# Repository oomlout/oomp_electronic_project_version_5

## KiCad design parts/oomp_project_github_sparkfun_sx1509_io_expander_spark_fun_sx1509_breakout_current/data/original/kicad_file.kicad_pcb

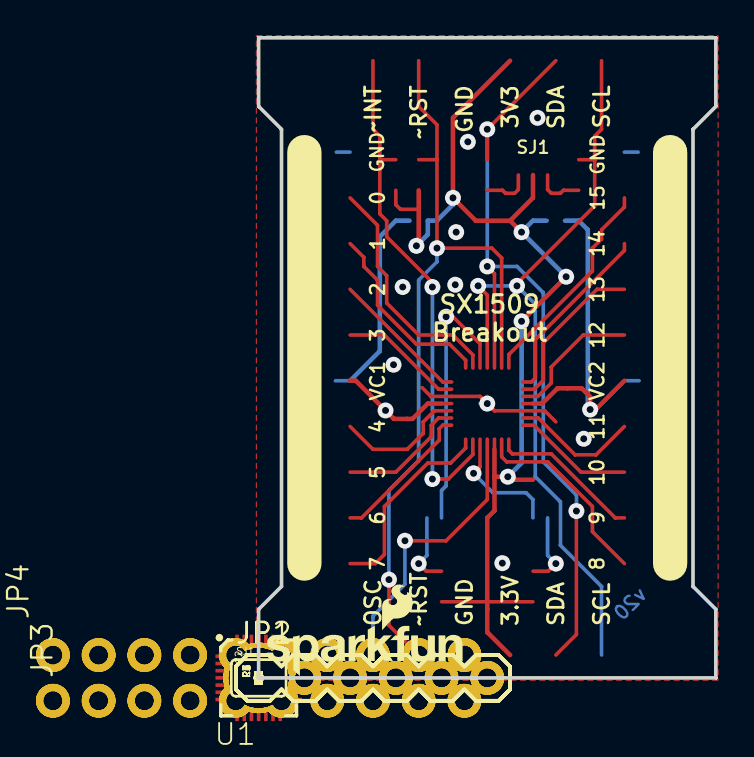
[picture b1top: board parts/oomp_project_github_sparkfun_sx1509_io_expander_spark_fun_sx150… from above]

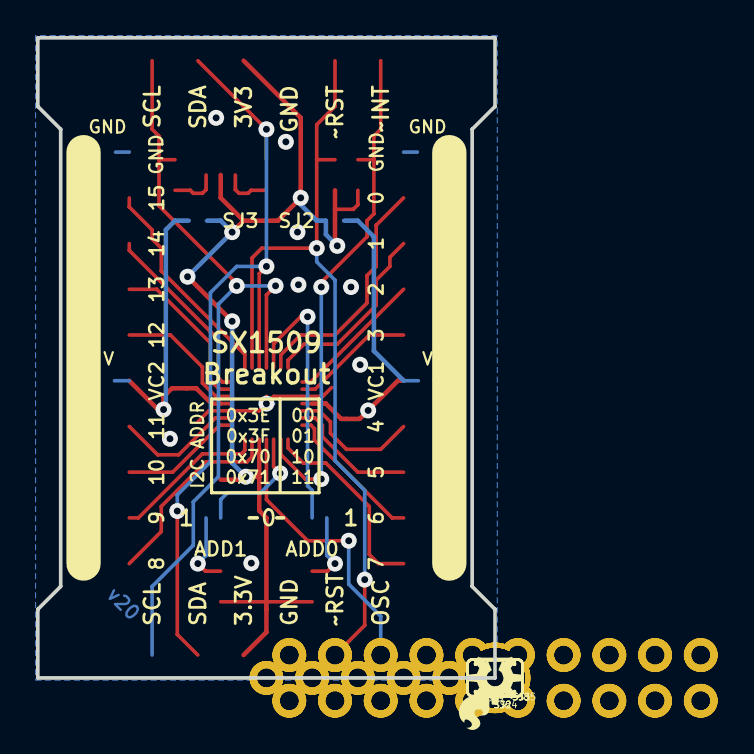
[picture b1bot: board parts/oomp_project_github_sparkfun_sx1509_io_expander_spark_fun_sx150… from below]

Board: 2 copper layers, 25.4 x 35.6 mm, 33 parts (10 on the bottom side), 33 nets.

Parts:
C1, C2, C3: 0.1uF; 0603-CAP
FRAME1: CREATIVE_COMMONS
JP1, JP2: 1X06
JP3, JP4: 2X10_ROUND_NOSILK
JP9, JP10: FIDUCIAL1X2; FIDUCIAL-1X2
LOGO1: SFE_LOGO_NAME_FLAME.1_INCH; SFE_LOGO_NAME_FLAME_.1
LOGO2: SFE_LOGO_FLAME.1_INCH; SFE_LOGO_FLAME_.1
LOGO3: OSHW-LOGOS; OSHW-LOGO-S
R1, R2, R3, R4, R5, R6: 10K; 0603-RES
SJ1: PAD-JUMPER-3-3OF3_NC_BY_TRACE_YES_SILK_FULL_BOX
SJ2: VCC1-3.3V; PAD-JUMPER-2-NC_BY_TRACE_YES_SILK
SJ3: VCC2-3.3V; PAD-JUMPER-2-NC_BY_TRACE_YES_SILK
SJ4, SJ5: PAD-JUMPER-3-2OF3_NC_BY_TRACE_YES_SILK_FULL_BOX
SJ6: A-VCC1; PAD-JUMPER-2-NO_NO_SILK
SJ7, SJ9: GND; PAD-JUMPER-2-NC_BY_TRACE_NO_SILK
SJ8: B-VCC2; PAD-JUMPER-2-NO_NO_SILK
STANDOFF1, STANDOFF2, STANDOFF3, STANDOFF4: STAND-OFF
U1: SX1509; QFN-28

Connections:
0: JP3.4, U1.27
1: JP3.6, U1.28
2: JP3.8, U1.1
3: JP3.10, U1.2
3.3V: C1.1, JP1.4, JP2.4, R1.2, R3.2, R5.2, R6.2, SJ1.2, SJ2.2, SJ3.2, U1.12
4: JP3.14, U1.5
5: JP3.16, U1.6
6: JP3.18, U1.7
7: JP3.20, U1.8
8: JP4.2, U1.13
9: JP4.4, U1.14
10: JP4.6, U1.15
11: JP4.8, U1.16
12: JP4.12, U1.19
13: JP4.14, U1.20
14: JP4.16, U1.21
15: JP4.18, U1.22
ADDR0: SJ4.2, U1.26
ADDR1: SJ5.2, U1.10
GND: C1.2, C2.2, C3.2, JP1.3, JP2.3, JP3.2, JP4.20, SJ4.3, SJ5.3, SJ7.1, SJ9.1, U1.3, U1.17, U1.29
unnamed: R2.2, SJ1.3
unnamed: R4.2, SJ1.1
unnamed: JP4.1, JP4.3, JP4.5, JP4.7, JP4.9, JP4.11, JP4.13, JP4.15, JP4.17, JP4.19, SJ8.1, SJ9.2
unnamed: R5.1, SJ4.1
unnamed: R6.1, SJ5.1
OSCIO: JP2.1, U1.11
PWRBUSA: JP3.1, JP3.3, JP3.5, JP3.7, JP3.9, JP3.11, JP3.13, JP3.15, JP3.17, JP3.19, SJ6.1, SJ7.2
SCL: JP1.6, JP2.6, R2.1, U1.25
SDA: JP1.5, JP2.5, R4.1, U1.24
VCC1: C2.1, JP3.12, SJ2.1, SJ6.2, U1.4
VCC2: C3.1, JP4.10, SJ3.1, SJ8.2, U1.18
~INT: JP1.1, R1.1, U1.9
~RESET: JP1.2, JP2.2, R3.1, U1.23

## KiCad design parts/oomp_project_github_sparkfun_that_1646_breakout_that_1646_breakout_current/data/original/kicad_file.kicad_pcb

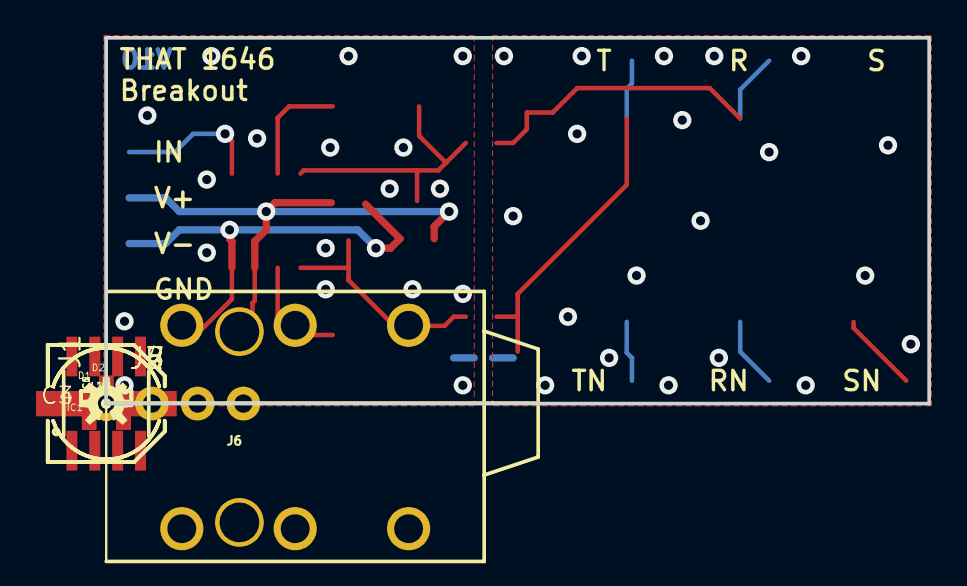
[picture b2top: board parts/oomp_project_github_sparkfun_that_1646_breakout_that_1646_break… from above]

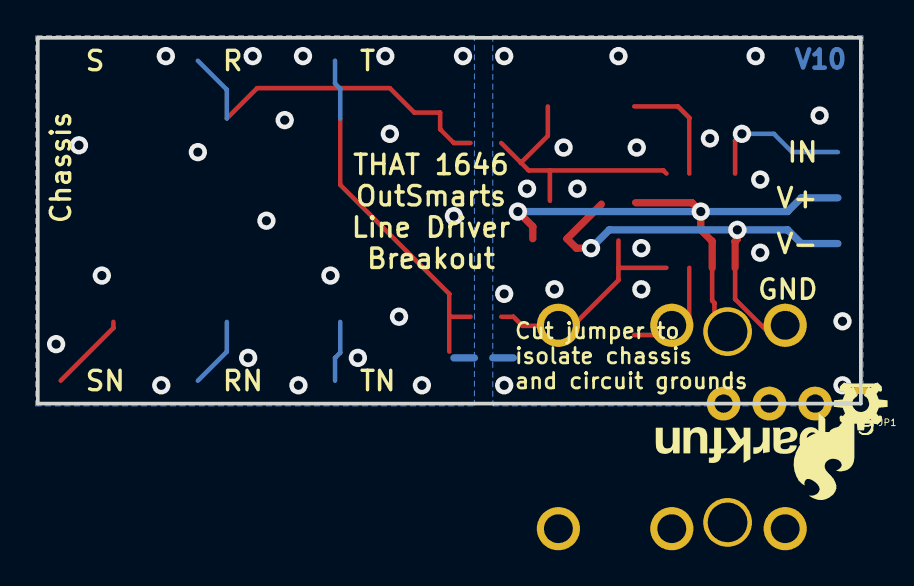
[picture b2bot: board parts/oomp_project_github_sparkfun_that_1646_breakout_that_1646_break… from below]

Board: 2 copper layers, 45.7 x 20.3 mm, 30 parts (8 on the bottom side), 14 nets.

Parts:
C1, C2: 0.1uF; 0603-CAP
C3, C4: 10uf NP; PANASONIC_D
C5, C6: 100pF; 0603-CAP
D1, D2: BAV99; SOT23-3
FD1, FD2, FD3, FD4: FIDUCIALUFIDUCIAL; MICRO-FIDUCIAL
FRAME1: FRAME-LETTER; CREATIVE_COMMONS
IC1: THAT1646; SO08
J1: 1x4; 1X04_NO_SILK_ALL_ROUND
J2: SN; 1X01_NO_SILK
J3: S; 1X01_NO_SILK
J4: TN; 1X01_NO_SILK
J5: RN; 1X01_NO_SILK
J6: OUTPUT; AUDIO_JACK_0.25__TRS_PTH_RA
J7: T; 1X01_NO_SILK
J8: R; 1X01_NO_SILK
J9: Chassis; 1X01_NO_SILK
JP1: GND-JOIN; PAD-JUMPER-2-NC_BY_TRACE_YES_SILK
L1, L2: 27uH; 0603
LOGO1, LOGO2: OSHW-LOGOS; OSHW-LOGO-S
LOGO4: SFE_LOGO_FLAME.2_INCH; SFE_LOGO_FLAME_.2
LOGO5: SFE_LOGO_NAME.1_INCH; SFE_LOGO_NAME_.1

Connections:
GND: C1.1, C2.1, IC1.3, J1.1, JP1.2
GND-ISO: C5.2, C6.2, J3.1, J6.SLEEVE, J9.1, JP1.1
unnamed: J5.1, J6.RING-NORM
unnamed: J4.1, J6.TIP-NORM
unnamed: J2.1, J6.SLEEVE-NORM
unnamed: C5.1, J6.TIP, J7.1, L2.2
unnamed: C6.1, J6.RING, J8.1, L1.2
unnamed: C3.-, D1.3, IC1.8, L2.1
unnamed: C4.-, D2.3, IC1.1, L1.1
unnamed: C4.+, IC1.2
unnamed: C3.+, IC1.7
unnamed: IC1.4, J1.4
VCC: C1.2, D1.2, D2.2, IC1.6, J1.3
VNEG: C2.2, D1.1, D2.1, IC1.5, J1.2

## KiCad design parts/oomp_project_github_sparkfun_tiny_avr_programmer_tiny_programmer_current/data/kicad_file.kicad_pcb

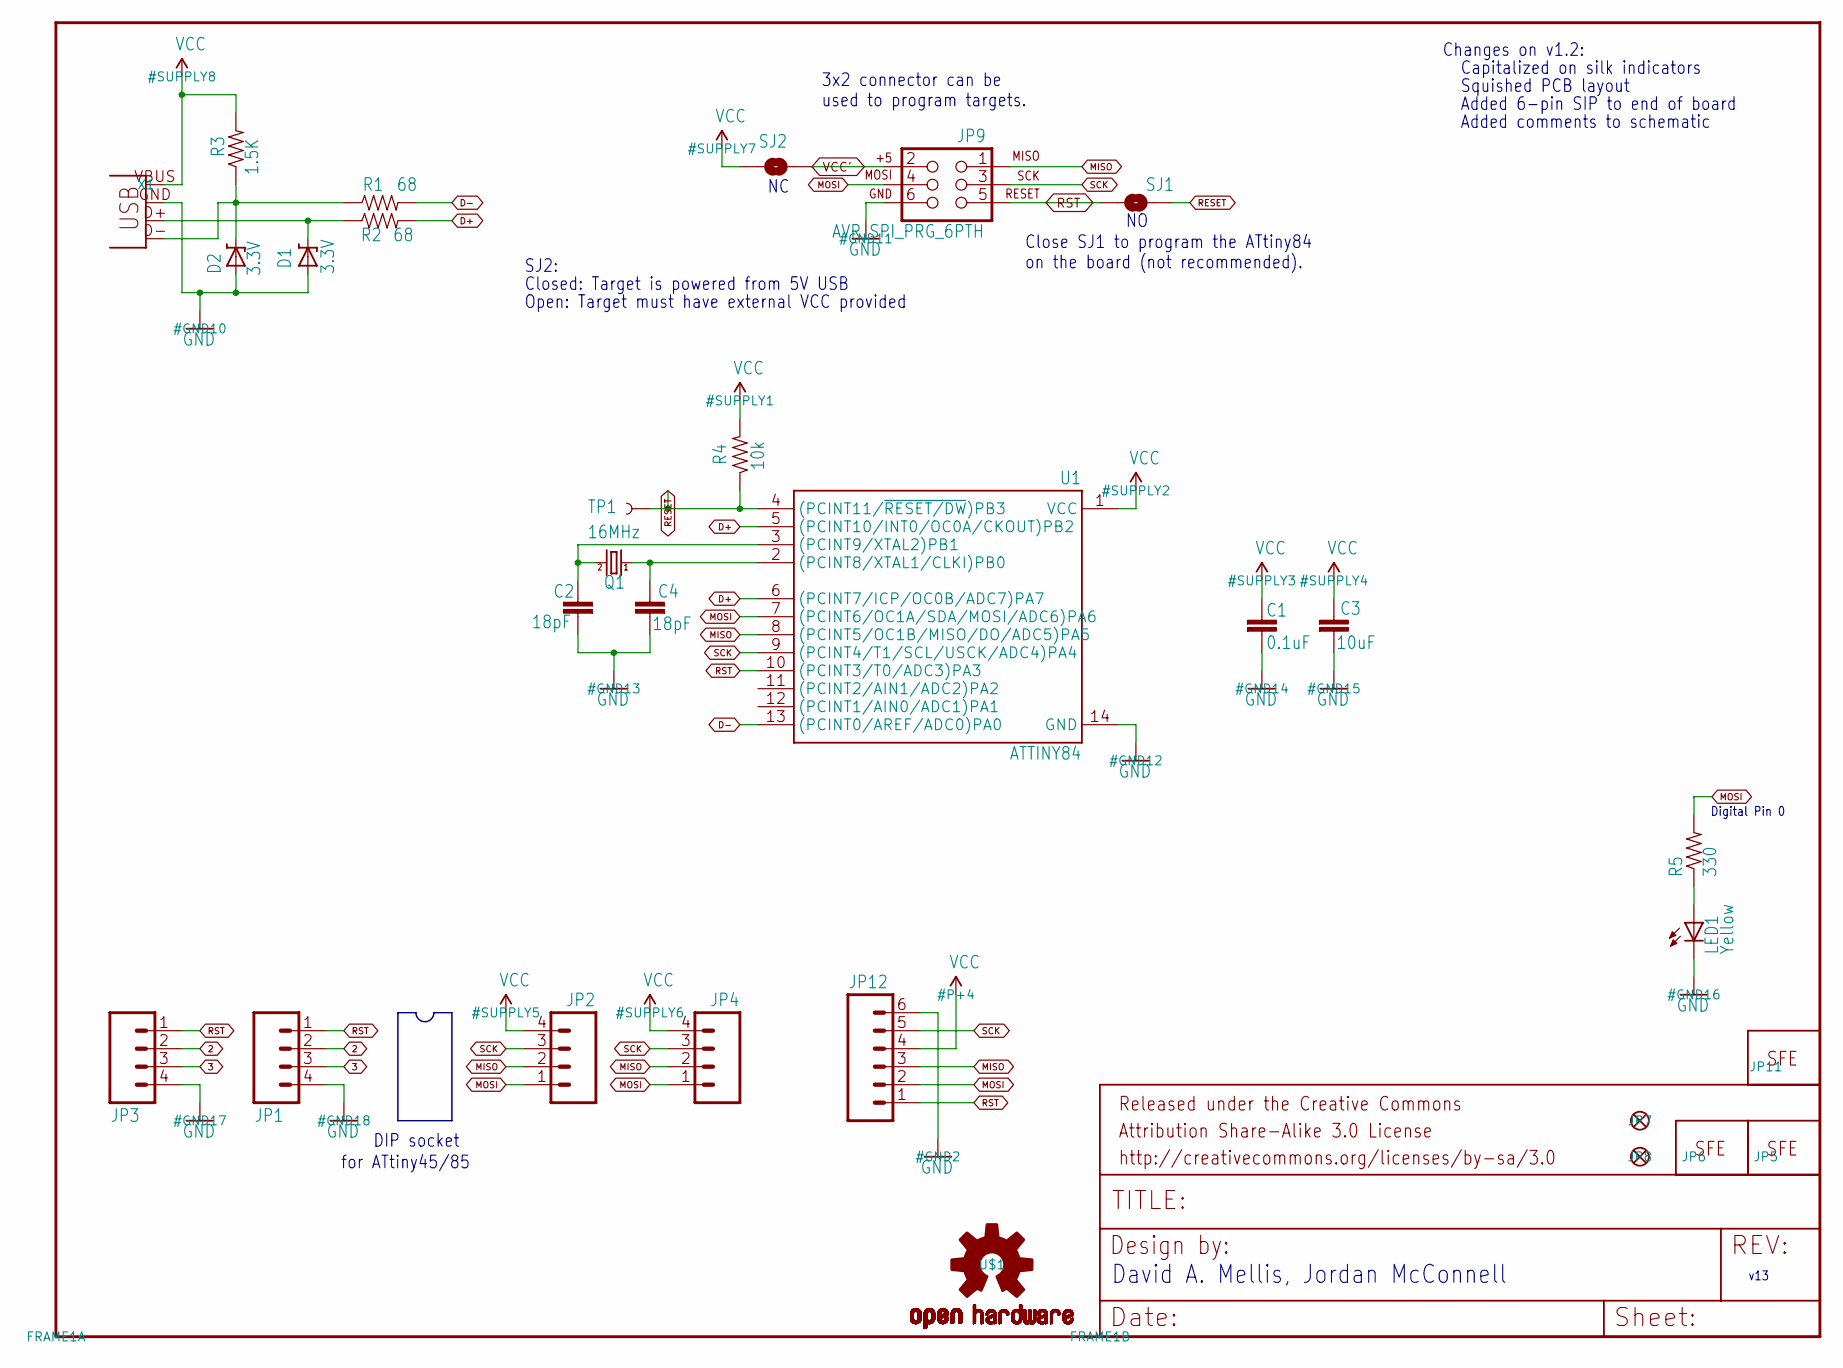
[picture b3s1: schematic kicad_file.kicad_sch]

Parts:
C1: 0.1uF; 0402-CAP
C2, C4: 18pF; 0402-CAP
C3: 10uF; 0402-CAP
D1, D2: 3.3V; SOD-323
FRAME1: FRAME-LETTER; CREATIVE_COMMONS
JP1, JP2: M04PTH; 1X04
JP3, JP4: M04SMD_STRAIGHT_COMBO; 1X04_SMD_STRAIGHT_COMBO
JP5: LOGO-SFENW2; SFE-NEW-WEB
JP6, JP11: LOGO-SFESK; SFE-LOGO-FLAME
JP7, JP8: FIDUCIALUFIDUCIAL; MICRO-FIDUCIAL
JP9: AVR_SPI_PRG_6PTH; 2X3
JP12: M06SIP; 1X06
LED1: Yellow; LED-0603
Q1: 16MHz; CRYSTAL-SMD-5X3
R1, R2: 68; 0402-RES
R3: 1.5K; 0402-RES
R4: 10k; 0402-RES
R5: 330; 0402-RES
SJ1: SOLDERJUMPERNO; SJ_2S-NO
SJ2: NC; SJ_2S
TP1: TEST-POINT3; PAD.03X.03
U1: ATTINY84; SO14
U$1: OSHW-LOGOS; OSHW-LOGO-S
X1: USB-A-H

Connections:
2: JP1.2, JP3.2
3: JP1.3, JP3.3
D+: R2.2, U1.5 ((PCINT10/INT0/OC0A/CKOUT)PB2), U1.6 ((PCINT7/ICP/OC0B/ADC7)PA7)
D-: R1.2, U1.13 ((PCINT0/AREF/ADC0)PA0)
GND: C1.2, C2.2, C3.2, C4.2, D1.2 (A), D2.2 (A), JP1.4, JP3.4, JP9.6, JP12.6, LED1.C, U1.14 (GND), X1.GND (VBUS)
MISO: JP2.2, JP4.2, JP9.1, JP12.3, U1.8 ((PCINT5/OC1B/MISO/DO/ADC5)PA5)
MOSI: JP2.1, JP4.1, JP9.4, JP12.2, R5.2, U1.7 ((PCINT6/OC1A/SDA/MOSI/ADC6)PA6)
unnamed: D2.1 (C), R1.1, R3.1, X1.D- (D+)
unnamed: D1.1 (C), R2.1, X1.D+ (D-)
unnamed: C2.1, Q1.3 (2), U1.3 ((PCINT9/XTAL2)PB1)
unnamed: C4.1, Q1.1, U1.2 ((PCINT8/XTAL1/CLKI)PB0)
unnamed: LED1.A, R5.1
RESET: R4.1, SJ1.1, TP1.P$1, U1.4 ((PCINT11/~RESET/DW)PB3)
RST: JP1.1, JP3.1, JP9.5, JP12.1, SJ1.2, U1.10 ((PCINT3/T0/ADC3)PA3)
SCK: JP2.3, JP4.3, JP9.3, JP12.5, U1.9 ((PCINT4/T1/SCL/USCK/ADC4)PA4)
VCC: C1.1, C3.1, JP2.4, JP4.4, JP12.4, R3.2, R4.2, SJ2.1, U1.1 (VCC), X1.VBUS (GND)
VCC': JP9.2, SJ2.2

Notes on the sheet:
Closed: Target is powered from 5V USB
v13
Added comments to schematic
Open: Target must have external VCC provided
Added 6-pin SIP to end of board
Close SJ1 to program the ATtiny84 on the board (not recommended).
Digital Pin 0
SJ2:
DIP socket
for ATtiny45/85
Squished PCB layout
Capitalized on silk indicators
David A. Mellis, Jordan McConnell
Changes on v1.2:
3x2 connector can be used to program targets.

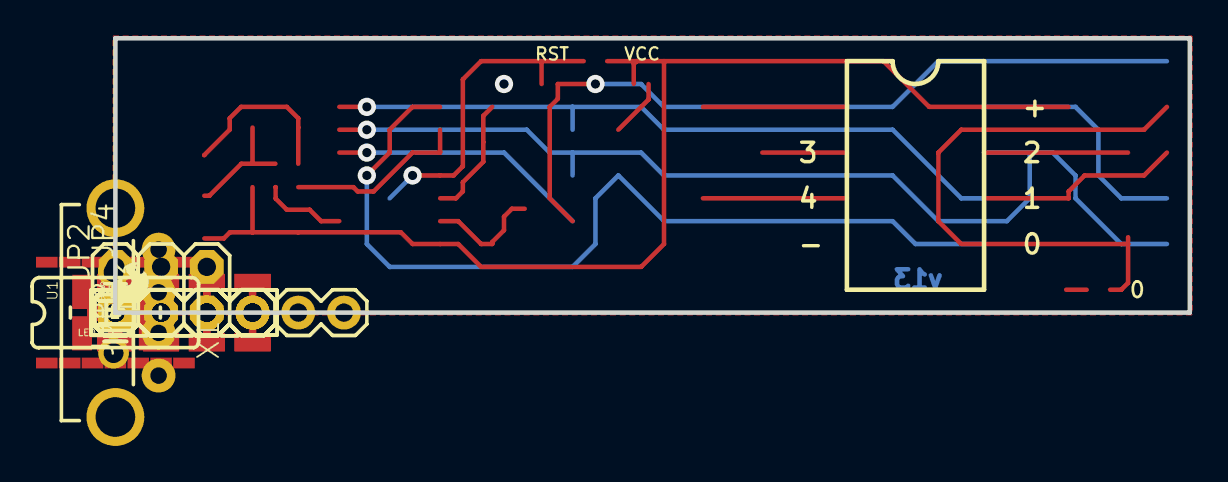
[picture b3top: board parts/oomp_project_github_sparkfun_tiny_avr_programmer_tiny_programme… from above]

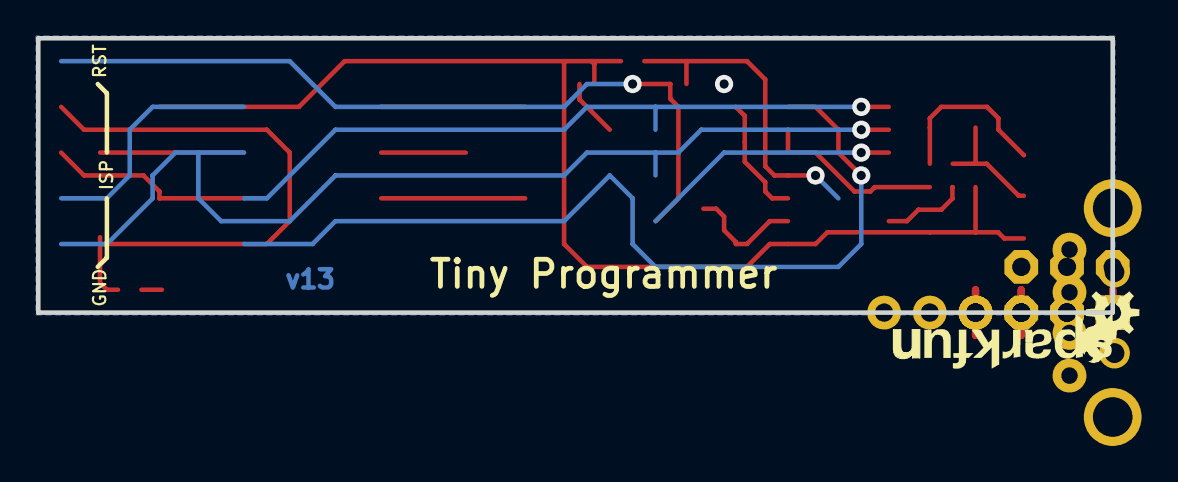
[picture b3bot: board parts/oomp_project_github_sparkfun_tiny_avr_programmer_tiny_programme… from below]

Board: 2 copper layers, 59.7 x 15.2 mm, 31 parts (4 on the bottom side), 17 nets.

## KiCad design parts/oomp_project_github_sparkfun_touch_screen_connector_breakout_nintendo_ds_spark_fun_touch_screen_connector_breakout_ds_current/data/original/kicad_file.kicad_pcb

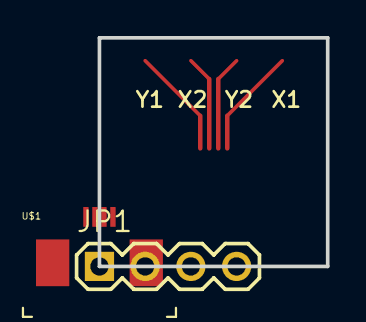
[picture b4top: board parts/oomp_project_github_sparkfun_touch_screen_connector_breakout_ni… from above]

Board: 16 copper layers, 12.7 x 12.7 mm, 5 parts (1 on the bottom side), 4 nets.

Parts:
FID1, FID2: FIDUCIAL1X2; FIDUCIAL-1X2
JP1: 1X04
U$1: DS_TOUCH_CONNECTOR
U$2: LOGO-SFESK; SFE-LOGO-FLAME

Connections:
unnamed: JP1.4, U$1.X1
unnamed: JP1.3, U$1.Y2
unnamed: JP1.2, U$1.X2
unnamed: JP1.1, U$1.Y1

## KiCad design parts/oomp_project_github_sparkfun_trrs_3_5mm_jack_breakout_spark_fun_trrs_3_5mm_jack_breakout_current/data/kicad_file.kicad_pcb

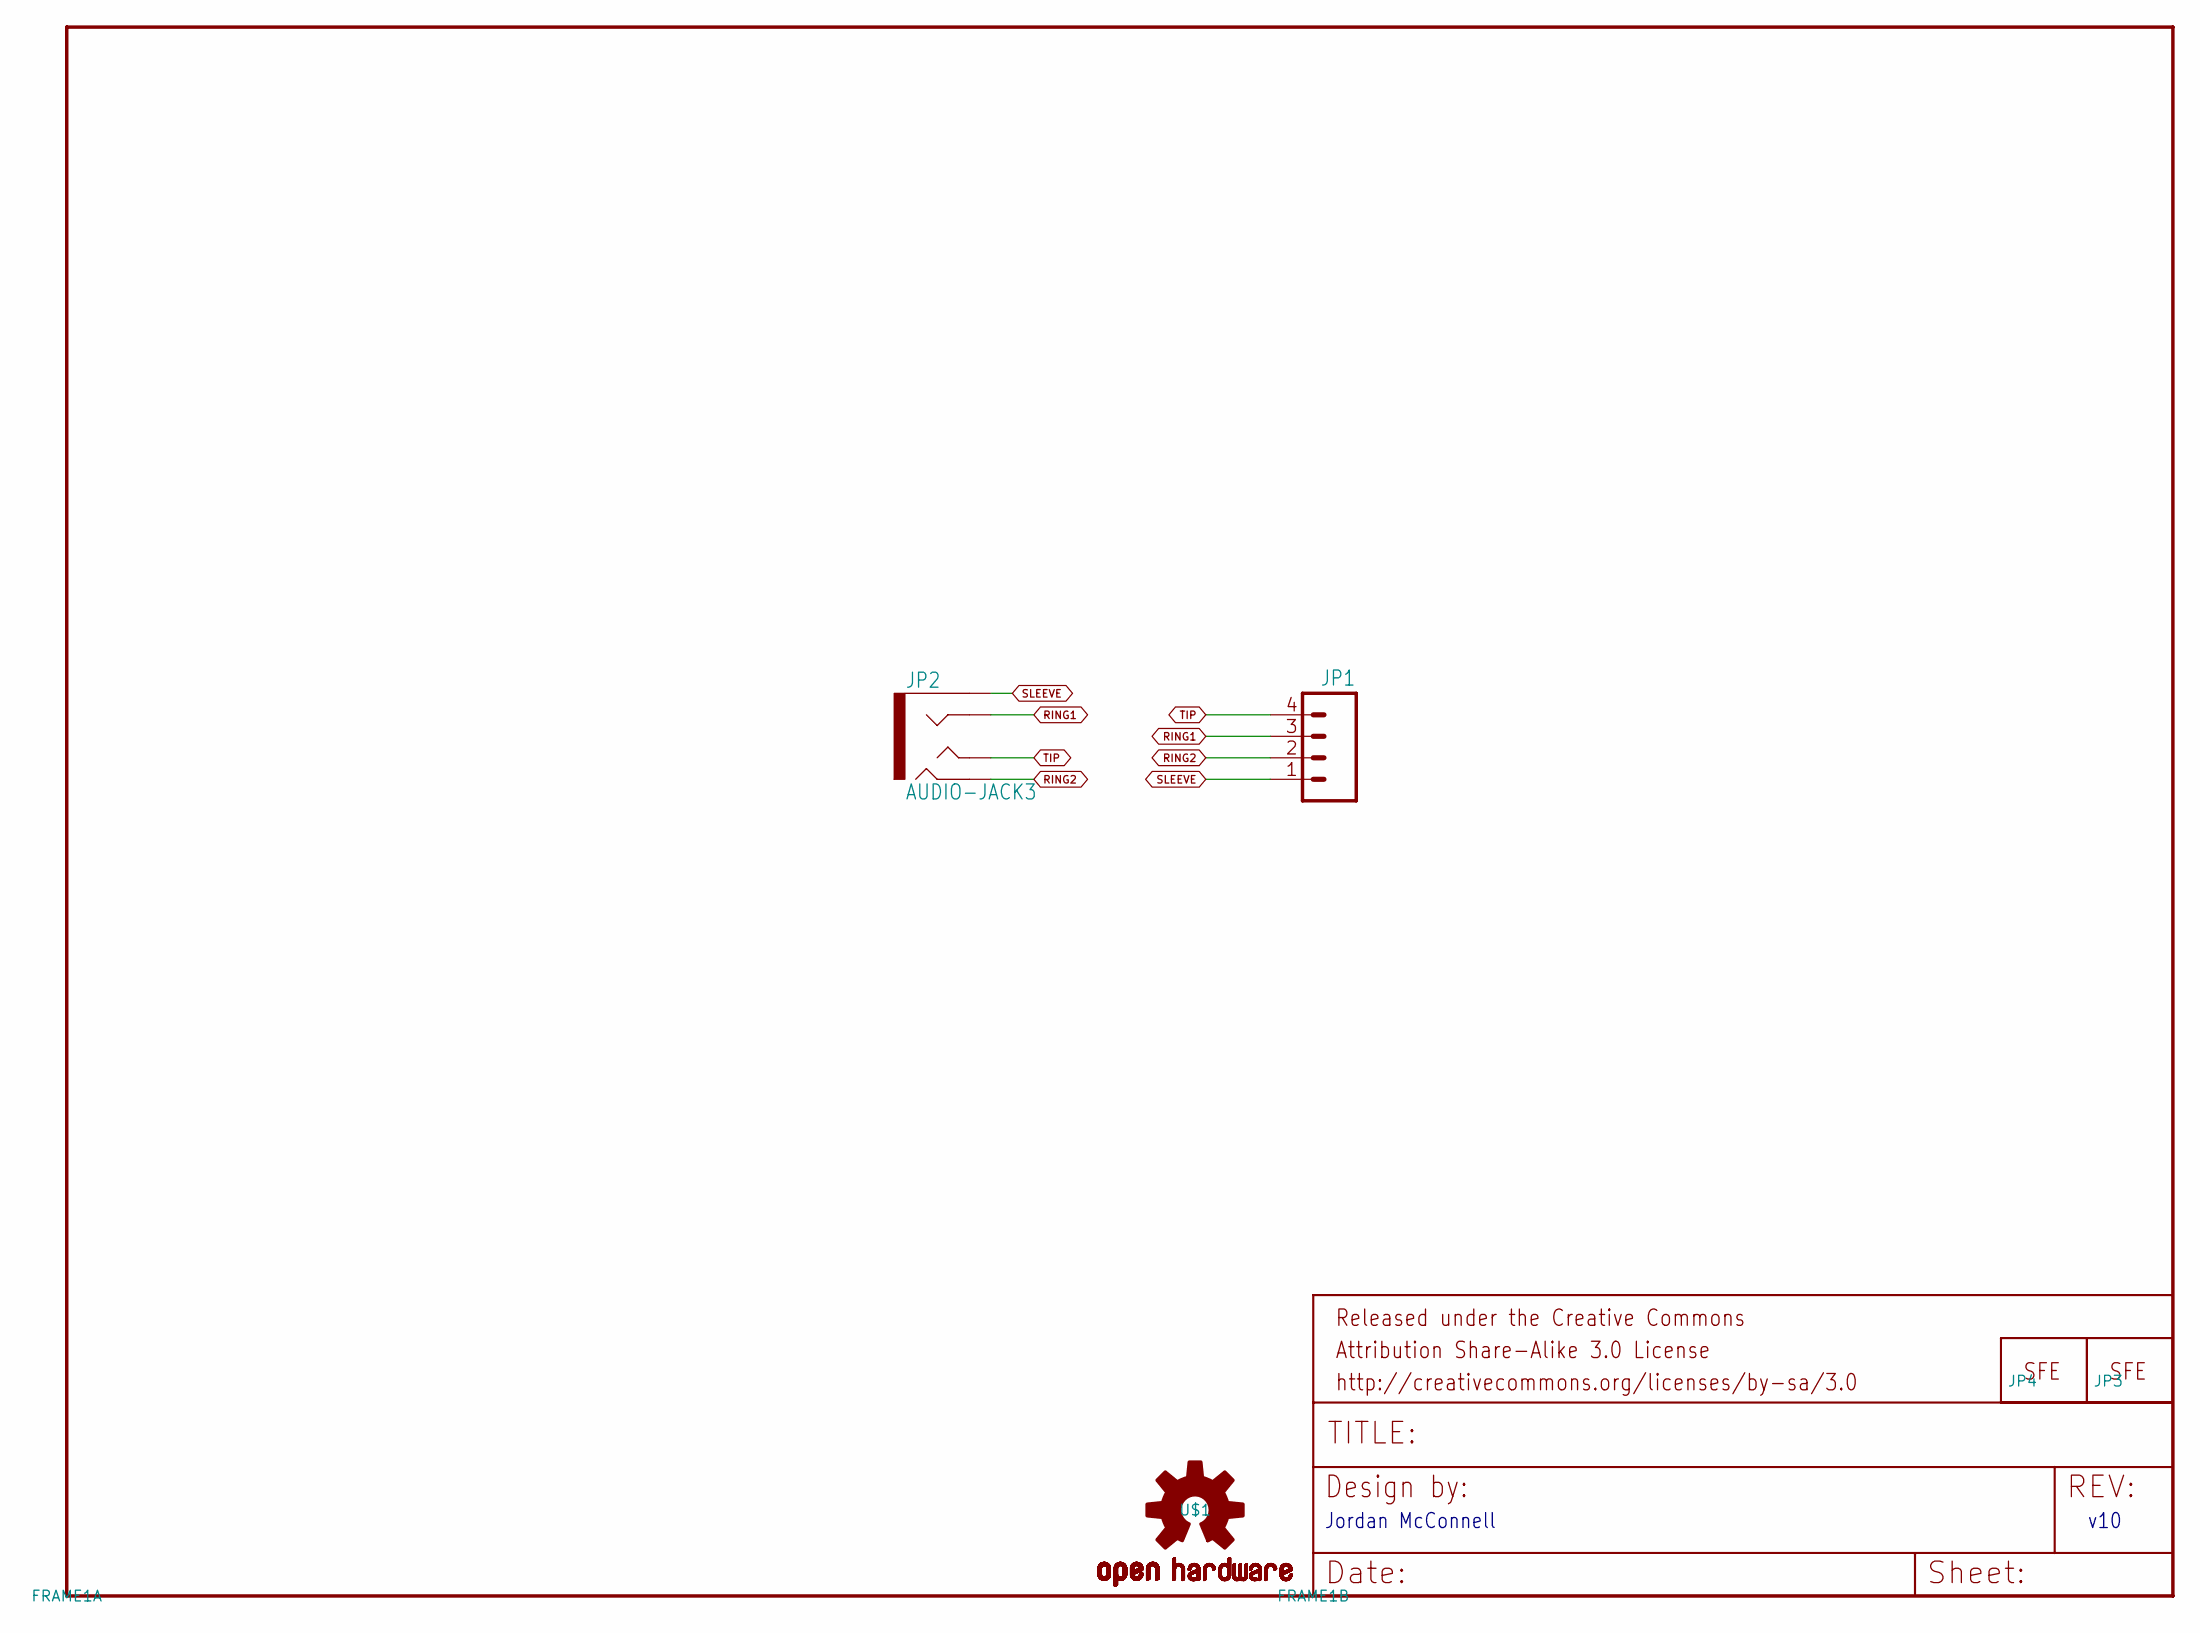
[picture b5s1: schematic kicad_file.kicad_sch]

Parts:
FRAME1: FRAME-LETTER; CREATIVE_COMMONS
JP1: M04PTH; 1X04
JP2: AUDIO-JACK3; AUDIO-JACK-TRRS-SMD
JP3, JP4: LOGO-SFESK; SFE-LOGO-FLAME
U$1: OSHW-LOGOS; OSHW-LOGO-S

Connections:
RING1: JP1.3, JP2.RING1
RING2: JP1.2, JP2.RING2
SLEEVE: JP1.1, JP2.EARTH
TIP: JP1.4, JP2.TIP

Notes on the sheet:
v10
Jordan McConnell

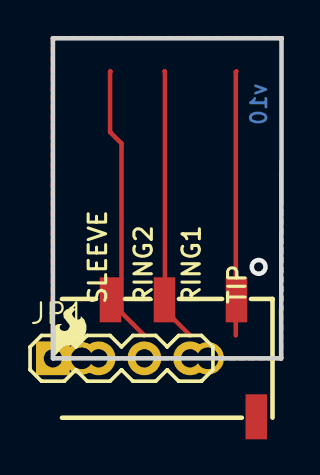
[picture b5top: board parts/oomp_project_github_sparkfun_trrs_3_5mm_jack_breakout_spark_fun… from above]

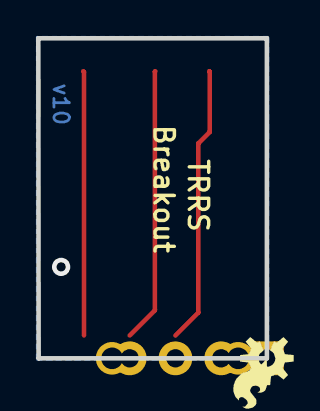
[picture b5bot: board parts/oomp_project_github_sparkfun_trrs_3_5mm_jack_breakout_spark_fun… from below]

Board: 2 copper layers, 12.7 x 17.8 mm, 6 parts (2 on the bottom side), 4 nets.

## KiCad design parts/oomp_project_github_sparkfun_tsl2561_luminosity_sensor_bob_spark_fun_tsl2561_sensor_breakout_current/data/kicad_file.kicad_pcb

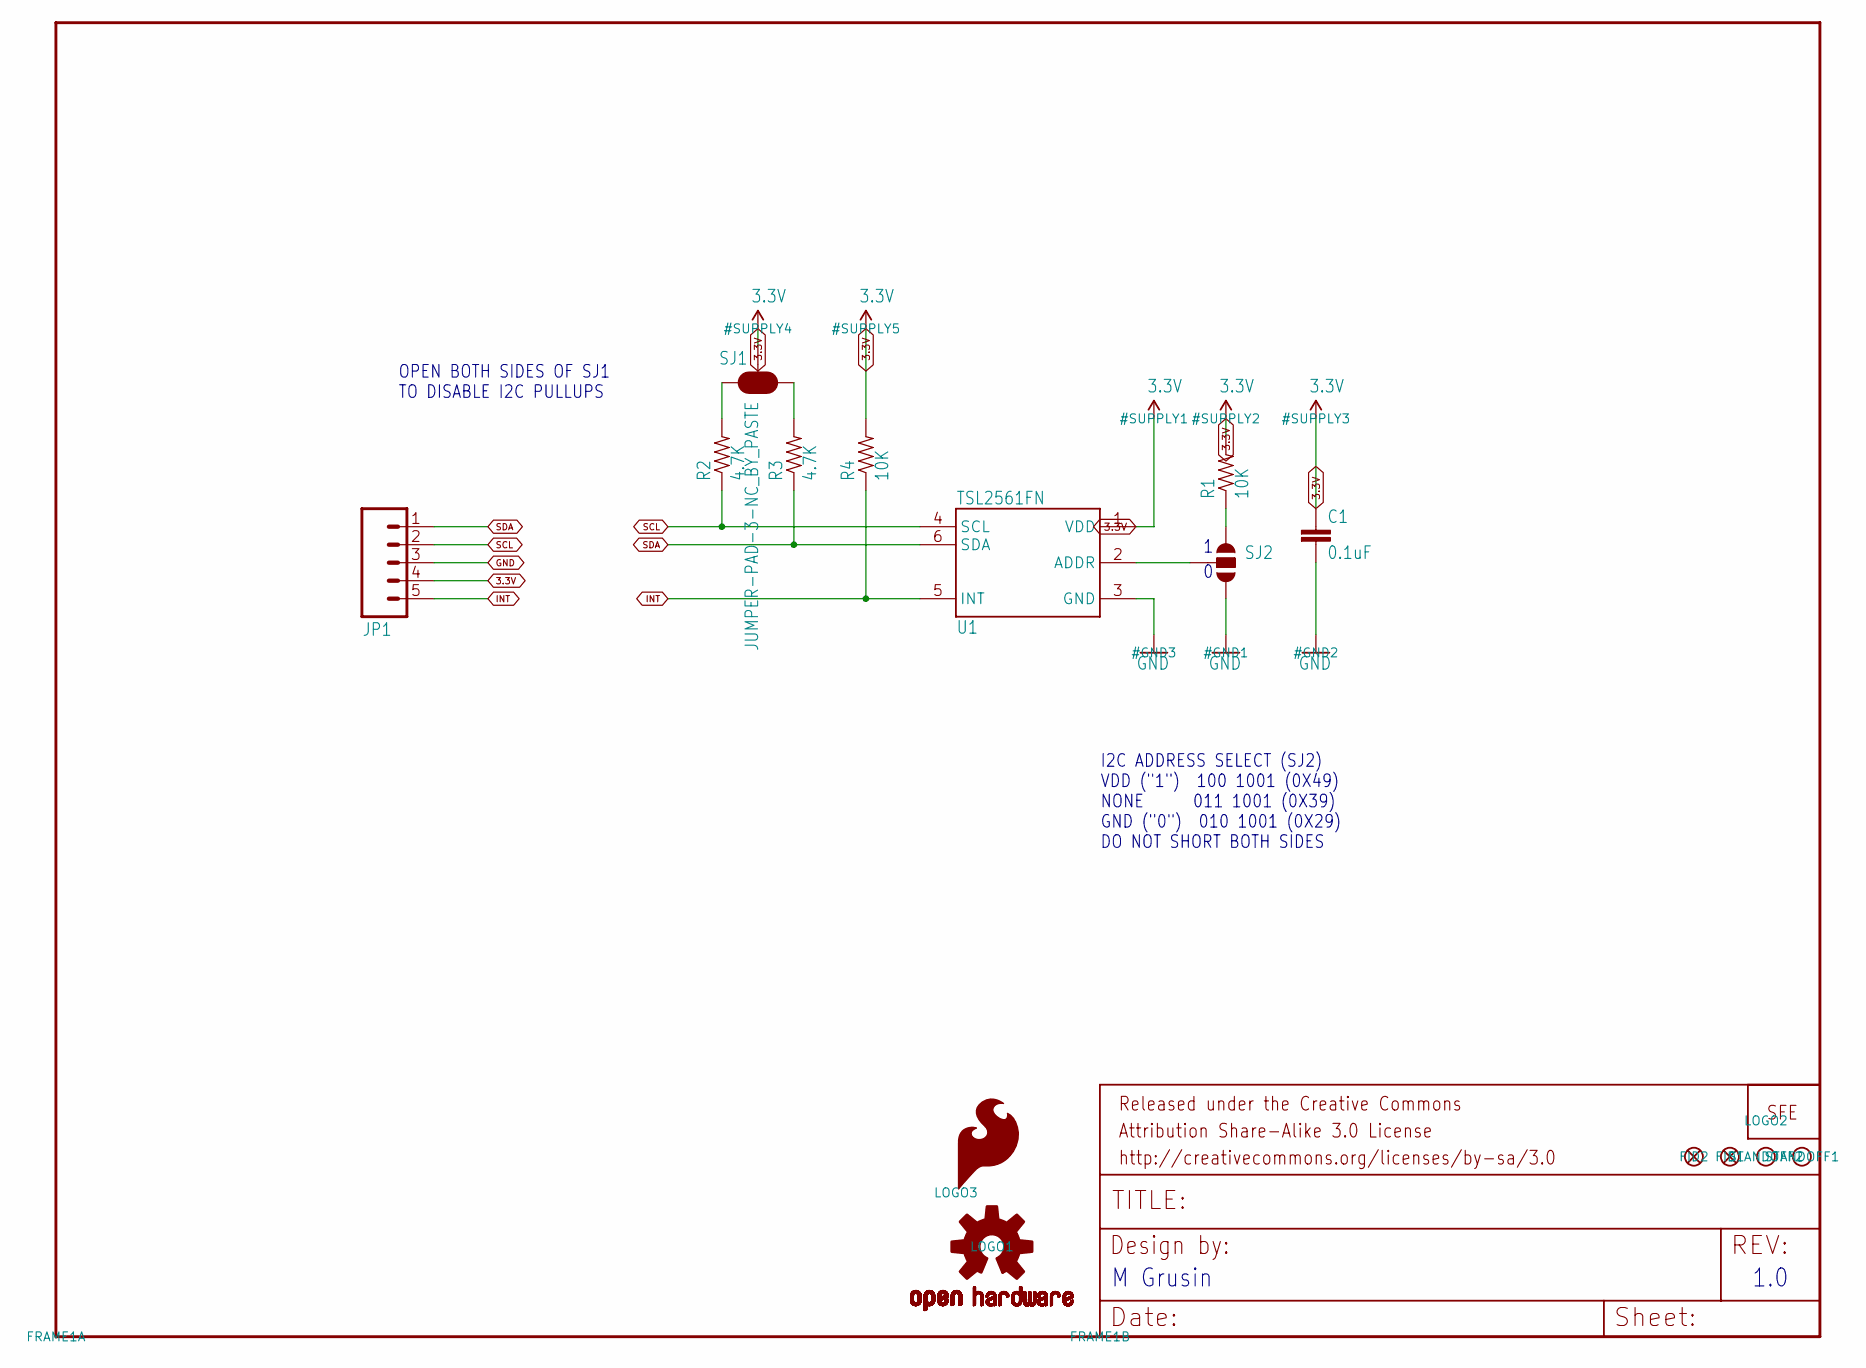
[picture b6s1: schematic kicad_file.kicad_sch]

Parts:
C1: 0.1uF; 0603-CAP
FID1, FID2: FIDUCIALUFIDUCIAL; MICRO-FIDUCIAL
FRAME1: FRAME-LETTER; CREATIVE_COMMONS
JP1: M05NO_SILK; 1X05_NO_SILK
LOGO1: OSHW-LOGOS; OSHW-LOGO-S
LOGO2: LOGO-SFENW2; SFE-NEW-WEB
LOGO3: SFE_LOGO_FLAME.1_INCH; SFE_LOGO_FLAME_.1
R1, R4: 10K; 0603-RES
R2, R3: 4.7K; 0603-RES
SJ1: JUMPER-PAD-3-NC_BY_PASTE; PAD-JUMPER-3-NC_BY_PASTE_YES_SILK_FULL_BOX
SJ2: SOLDERJUMPER_2WAYS; SJ_3
STANDOFF1, STANDOFF2: STAND-OFF
U1: TSL2561FN; FN-6

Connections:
3.3V: C1.1, JP1.4, R1.2, R4.2, SJ1.2, U1.1 (VDD)
GND: C1.2, JP1.3, SJ2.3, U1.3 (GND)
INT: JP1.5, R4.1, U1.5 (INT)
unnamed: R1.1, SJ2.1
unnamed: SJ2.2, U1.2 (ADDR)
unnamed: R3.2, SJ1.1
unnamed: R2.2, SJ1.3
SCL: JP1.2, R2.1, U1.4 (SCL)
SDA: JP1.1, R3.1, U1.6 (SDA)

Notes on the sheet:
I2C ADDRESS SELECT (SJ2) VDD ("1") 100 1001 (0X49) NONE 011 1001 (0X39) GND ("0") 010 1001 (0X29) DO NOT SHORT BOTH SIDES
1.0
OPEN BOTH SIDES OF SJ1 TO DISABLE I2C PULLUPS
M Grusin

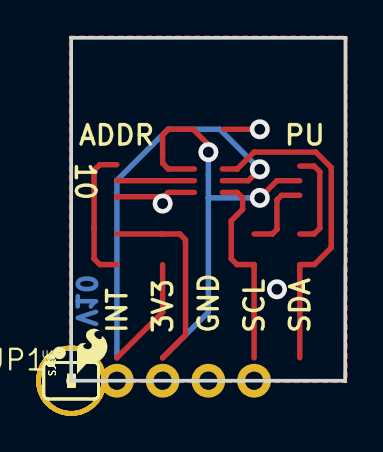
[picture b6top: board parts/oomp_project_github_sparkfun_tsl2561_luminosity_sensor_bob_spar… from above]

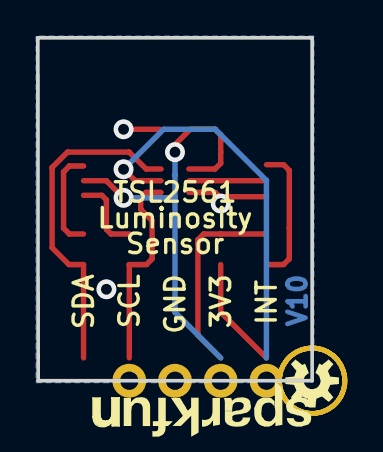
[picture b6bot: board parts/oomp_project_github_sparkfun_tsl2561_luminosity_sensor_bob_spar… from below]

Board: 2 copper layers, 15.2 x 19.1 mm, 17 parts (2 on the bottom side), 9 nets.

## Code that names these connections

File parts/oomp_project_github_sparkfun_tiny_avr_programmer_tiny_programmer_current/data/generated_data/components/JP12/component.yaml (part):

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        pin_name: '2'
      - reference: U1
        pin_number: '10'
        pin_name: (PCINT3/T0/ADC3)PA3
    - number: '2'
      name: '2'
      electrical_type: passive
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        pin_name: '2'
      - reference: U1
        pin_number: '7'
        pin_name: (PCINT6/OC1A/SDA/MOSI/ADC6)PA6
    - number: '3'
      name: '3'
      electrical_type: passive
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        pin_name: '1'
      - reference: U1
        pin_number: '8'
        pin_name: (PCINT5/OC1B/MISO/DO/ADC5)PA5
    - number: '4'
      name: '4'
      electrical_type: passive
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        pin_name: '3'
      - reference: U1
        pin_number: '9'
        pin_name: (PCINT4/T1/SCL/USCK/ADC4)PA4
    - number: '6'
      name: '6'
      electrical_type: passive
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    pin_name: VCC
  - reference: U1
    pin_number: '10'
    pin_name: (PCINT3/T0/ADC3)PA3
  - reference: U1
    pin_number: '14'
    pin_name: GND
  - reference: U1
    pin_number: '7'
    pin_name: (PCINT6/OC1A/SDA/MOSI/ADC6)PA6
  - reference: U1
    pin_number: '8'
    pin_name: (PCINT5/OC1B/MISO/DO/ADC5)PA5
  - reference: U1
    pin_number: '9'
    pin_name: (PCINT4/T1/SCL/USCK/ADC4)PA4
  - reference: X1
    pin_number: GND
    pin_name: VBUS
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
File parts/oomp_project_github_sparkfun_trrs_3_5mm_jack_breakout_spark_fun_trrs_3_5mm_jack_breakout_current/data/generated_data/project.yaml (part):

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        no_connect: false
        connected_to:
        - reference: JP2
          pin_number: RING2
          pin_name: RING2
      - number: '3'
        name: '3'
        electrical_type: passive
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        no_connect: false
        connected_to:
        - reference: JP2
          pin_number: RING1
          pin_name: RING1
      - number: '4'
        name: '4'
        electrical_type: passive
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        no_connect: false
        connected_to:
        - reference: JP2
          pin_number: TIP
          pin_name: TIP
      size:
        local_graphics:
          measurement: symbol graphics only; excludes pins, properties, and text
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      pin_number: EARTH
      pin_name: EARTH
    - reference: JP2
      pin_number: RING1
      pin_name: RING1
    - reference: JP2
      pin_number: RING2
      pin_name: RING2
    - reference: JP2
      pin_number: TIP
      pin_name: TIP
  pcb:
    reference: JP1
    value: ''
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      pcb_nets:
      - SLEEVE
      status: agree
    - pin_or_pad_number: RING1
      schematic_nets:
      - RING1
      pcb_nets:
      - RING1
      status: agree
    - pin_or_pad_number: RING2
      schematic_nets:
      - RING2
      pcb_nets:
      - RING2
      status: agree
    - pin_or_pad_number: TIP
      schematic_nets:
      - TIP
      pcb_nets:
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

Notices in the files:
parts/oomp_project_github_sparkfun_tiny_avr_programmer_tiny_programmer_current/data/original/kicad_file.kicad_sch:
Released under the Creative Commons
http://creativecommons.org/licenses/by-sa/3.0
parts/oomp_project_github_sparkfun_tsunami_tapestry_current/data/original/kicad_file.kicad_sch:
https://creativecommons.org/licenses/by-sa/4.0
parts and their libraries:
Released under the Creative Commons Attribution Share-Alike 4.0 License
Released under the Creative Commons Attribution Share-Alike 3.0 License
